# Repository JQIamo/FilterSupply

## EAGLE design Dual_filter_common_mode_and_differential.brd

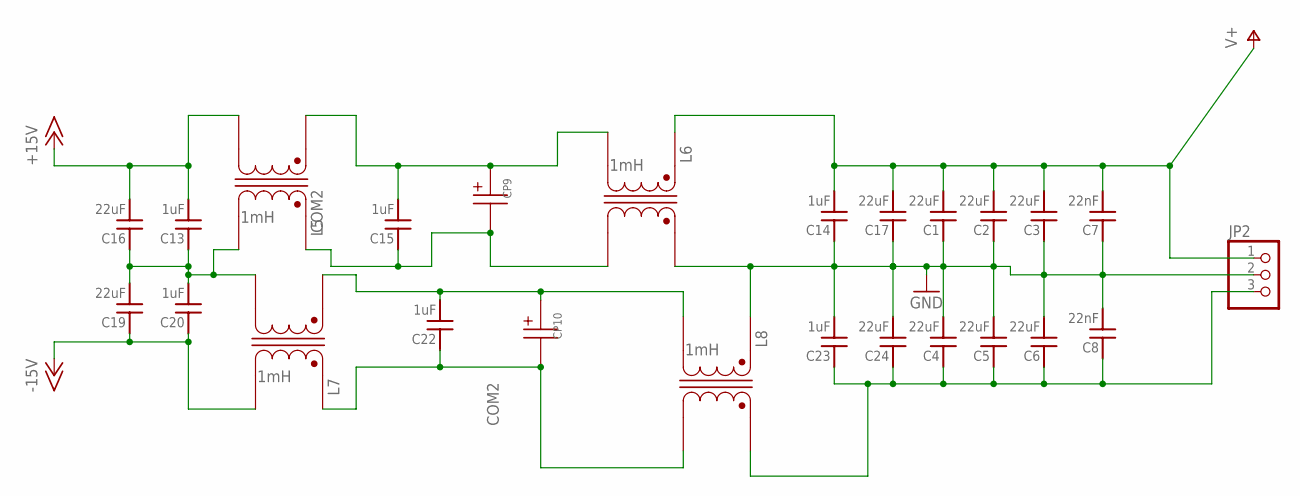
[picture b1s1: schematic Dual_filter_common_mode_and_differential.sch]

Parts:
C1, C2, C3, C4, C5, C6, C16, C17, C19, C24: 22uF; C_MLCC_0805; DIGIKEY 445-9112-1-ND
C7, C8: 22nF; C_MLCC_0306; DIGIKEY 490-4317-1-ND
C13, C14, C15, C20, C22, C23: 1uF; C_MLCC_0805; DIGIKEY 587-5018-1-ND
CP9, CP10: CAP-POLPANASONIC_F; PANASONIC_F
JP2: PINHD-1X3; 1X03; DIGIKEY WM4201-ND
L5, L6, L7, L8: 1mH; COILCRAFT_TRANSFORMER_MSD1260

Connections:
+15V2: C13.P$2 (2), C16.P$2 (2), L5.P$4 (4)
-15V2: C19.P$1 (1), C20.P$1 (1), L7.P$3 (3)
COM2: C13.P$1 (1), C16.P$1 (1), C19.P$2 (2), C20.P$2 (2), L5.P$3 (3), L7.P$4 (4)
GND2: C1.P$1 (1), C2.P$1 (1), C3.P$1 (1), C4.P$2 (2), C5.P$2 (2), C6.P$2 (2), C7.P$1 (1), C8.P$2 (2), C14.P$1 (1), C17.P$1 (1), C23.P$2 (2), C24.P$2 (2), JP2.2, L6.P$2 (2), L8.P$1 (1)
unnamed: C15.P$2 (2), CP9.+, L5.P$2 (2), L6.P$3 (3)
unnamed: C15.P$1 (1), CP9.-, L5.P$1 (1), L6.P$4 (4)
unnamed: C22.P$2 (2), CP10.+, L7.P$2 (2), L8.P$3 (3)
unnamed: C22.P$1 (1), CP10.-, L7.P$1 (1), L8.P$4 (4)
unnamed: C4.P$1 (1), C5.P$1 (1), C6.P$1 (1), C8.P$1 (1), C23.P$1 (1), C24.P$1 (1), JP2.3, L8.P$2 (2)
V+2: C1.P$2 (2), C2.P$2 (2), C3.P$2 (2), C7.P$2 (2), C14.P$2 (2), C17.P$2 (2), JP2.1, L6.P$1 (1)

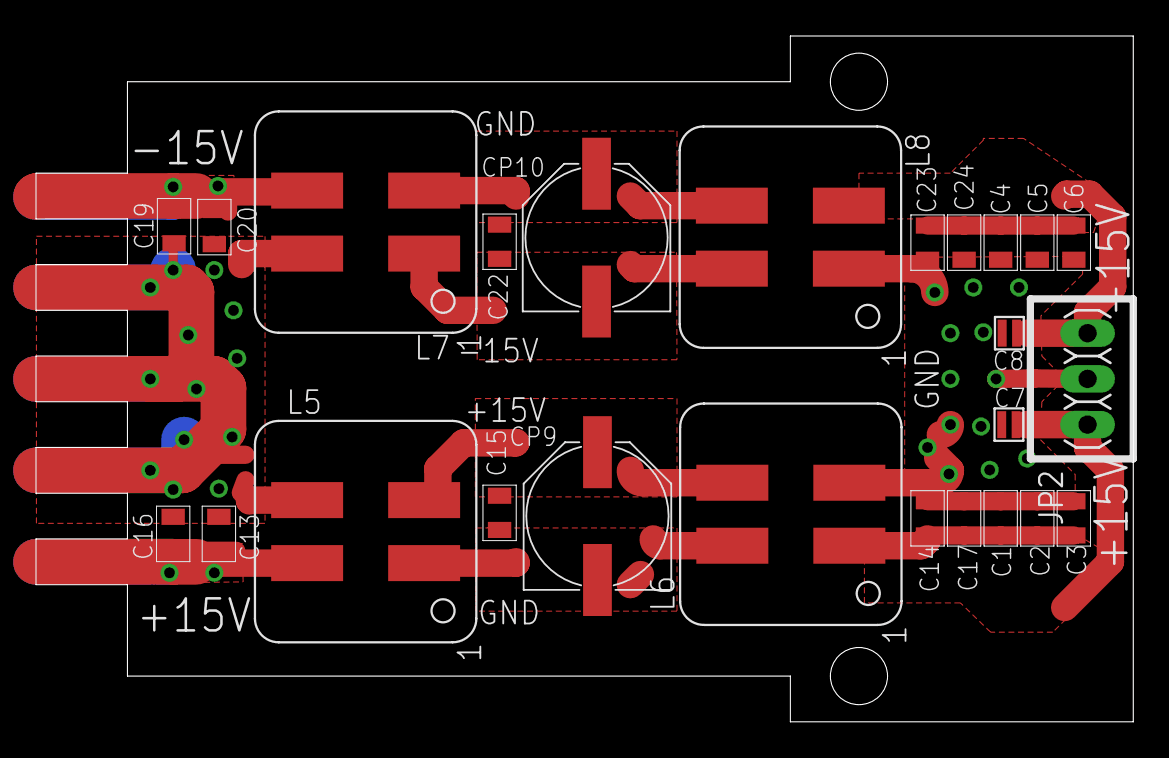
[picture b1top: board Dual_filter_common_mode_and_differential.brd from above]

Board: 2 copper layers, 61.0 x 38.1 mm, 25 parts (0 on the bottom side), 10 nets.

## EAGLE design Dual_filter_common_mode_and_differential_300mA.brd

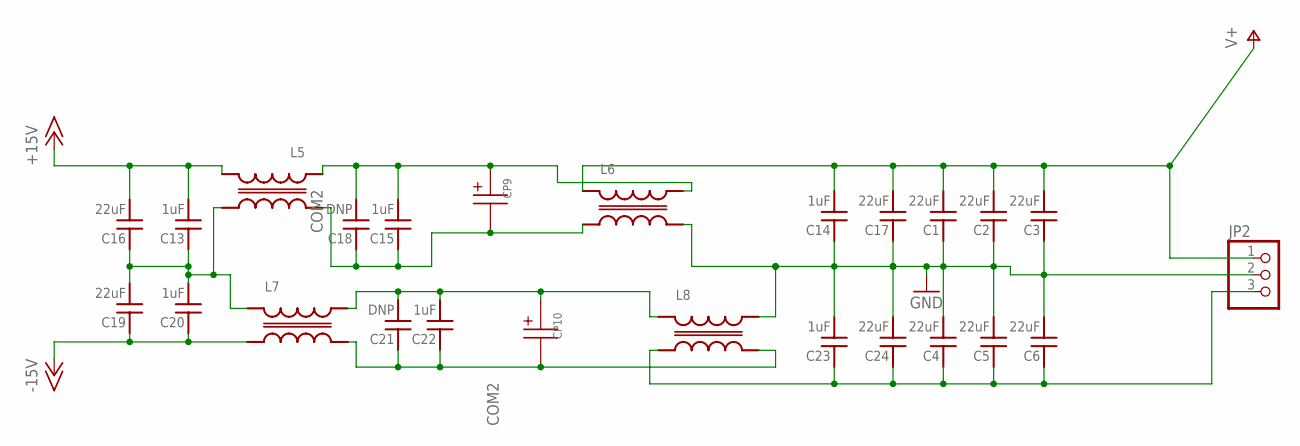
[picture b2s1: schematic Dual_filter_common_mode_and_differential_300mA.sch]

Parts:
C1, C2, C3, C4, C5, C6, C16, C17, C19, C24: 22uF; C_MLCC_0805; DIGIKEY 445-9112-1-ND
C13, C14, C15, C20, C22, C23: 1uF; C_MLCC_0805; DIGIKEY 587-5018-1-ND
C18, C21: DNP; C_MLCC_0805
CP9, CP10: CAP-POLPANASONIC_F; PANASONIC_F
JP2: PINHD-1X3; 1X03; DIGIKEY WM4201-ND
L5, L6, L7, L8: MSD7342

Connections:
+15V2: C13.P$2 (2), C16.P$2 (2), L5.4
-15V2: C19.P$1 (1), C20.P$1 (1), L7.1
COM2: C13.P$1 (1), C16.P$1 (1), C19.P$2 (2), C20.P$2 (2), L5.3, L7.2
GND2: C1.P$1 (1), C2.P$1 (1), C3.P$1 (1), C4.P$2 (2), C5.P$2 (2), C6.P$2 (2), C14.P$1 (1), C17.P$1 (1), C23.P$2 (2), C24.P$2 (2), JP2.2, L6.3, L8.4
unnamed: C15.P$2 (2), C18.P$2 (2), CP9.+, L5.2, L6.4
unnamed: C15.P$1 (1), C18.P$1 (1), CP9.-, L5.1, L6.1
unnamed: C21.P$2 (2), C22.P$2 (2), CP10.+, L7.4, L8.2
unnamed: C21.P$1 (1), C22.P$1 (1), CP10.-, L7.3, L8.3
unnamed: C4.P$1 (1), C5.P$1 (1), C6.P$1 (1), C23.P$1 (1), C24.P$1 (1), JP2.3, L8.1
V+2: C1.P$2 (2), C2.P$2 (2), C3.P$2 (2), C14.P$2 (2), C17.P$2 (2), JP2.1, L6.2

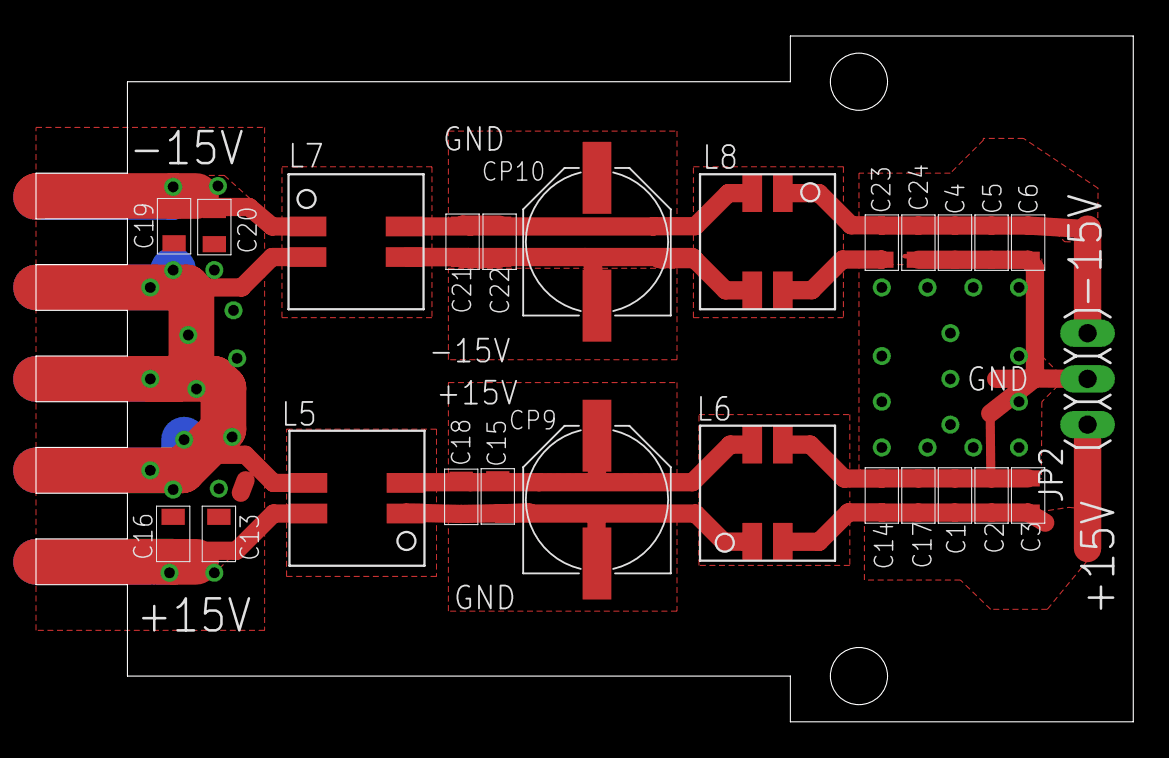
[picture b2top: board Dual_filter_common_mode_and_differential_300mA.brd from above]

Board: 2 copper layers, 61.0 x 38.1 mm, 25 parts (0 on the bottom side), 10 nets.

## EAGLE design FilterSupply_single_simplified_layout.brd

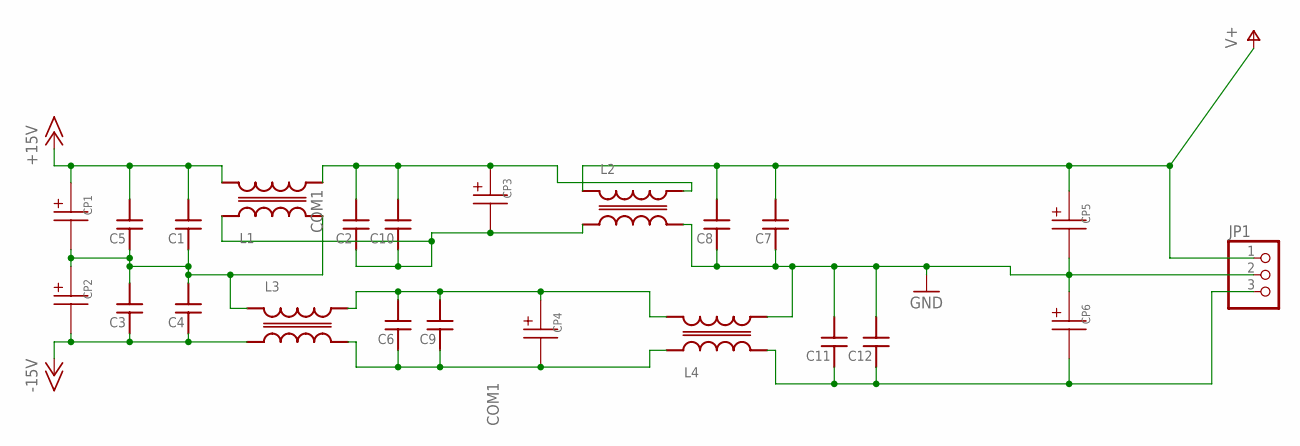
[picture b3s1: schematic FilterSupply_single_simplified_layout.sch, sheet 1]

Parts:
C1, C3, C4, C5: C_MLCC_SMDCMLCC_0805; C_MLCC_0805
C2, C6, C7, C8, C9, C10, C11, C12: C_MLCC_SMDCMLCC_0603; C_MLCC_0603
CP1, CP2, CP3, CP4, CP5, CP6: CAP-POLPANASONIC_F; PANASONIC_F
JP1: PINHD-1X3; 1X03
L1, L2, L3, L4: MSD7342

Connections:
+15V: C1.P$2 (2), C5.P$2 (2), CP1.+, L1.1
-15V: C3.P$1 (1), C4.P$1 (1), CP2.-, L3.1
COM1: C1.P$1 (1), C3.P$2 (2), C4.P$2 (2), C5.P$1 (1), CP1.-, CP2.+, L1.4, L3.2
GND: C7.P$1 (1), C8.P$1 (1), C11.P$2 (2), C12.P$2 (2), CP5.-, CP6.+, JP1.2, L2.3, L4.3
unnamed: C2.P$2 (2), C10.P$2 (2), CP3.+, L1.3, L2.4
unnamed: C2.P$1 (1), C10.P$1 (1), CP3.-, L1.2, L2.1
unnamed: C6.P$2 (2), C9.P$2 (2), CP4.+, L3.4, L4.1
unnamed: C6.P$1 (1), C9.P$1 (1), CP4.-, L3.3, L4.2
unnamed: C11.P$1 (1), C12.P$1 (1), CP6.-, JP1.3, L4.4
V+: C7.P$2 (2), C8.P$2 (2), CP5.+, JP1.1, L2.2

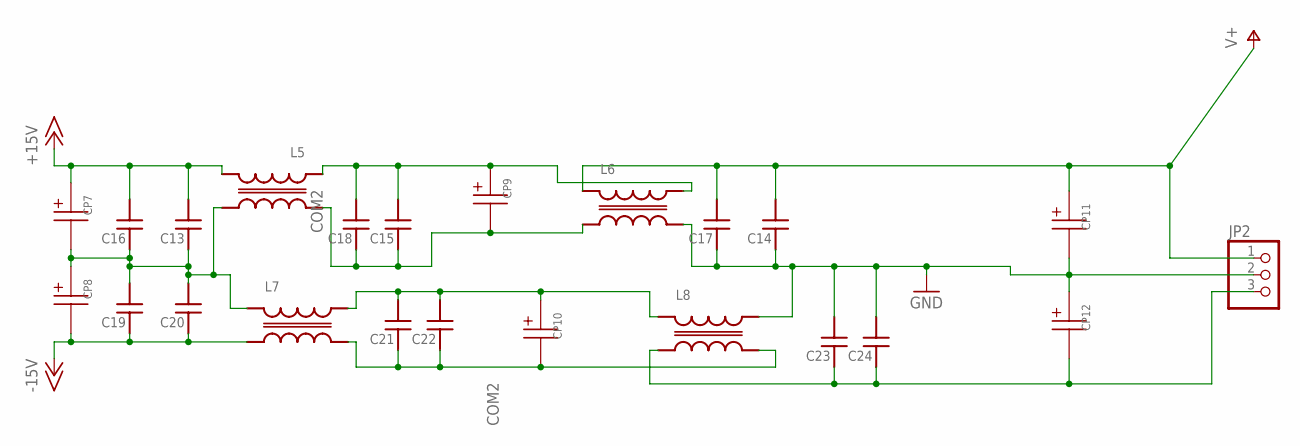
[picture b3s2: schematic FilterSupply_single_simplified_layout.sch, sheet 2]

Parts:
C13, C16, C19, C20: C_MLCC_SMDCMLCC_0805; C_MLCC_0805
C14, C15, C17, C18, C21, C22, C23, C24: C_MLCC_SMDCMLCC_0603; C_MLCC_0603
CP7, CP8, CP9, CP10, CP11, CP12: CAP-POLPANASONIC_F; PANASONIC_F
JP2: PINHD-1X3; 1X03
L5, L6, L7, L8: MSD7342

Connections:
+15V2: C13.P$2 (2), C16.P$2 (2), CP7.+, L5.4
-15V2: C19.P$1 (1), C20.P$1 (1), CP8.-, L7.1
COM2: C13.P$1 (1), C16.P$1 (1), C19.P$2 (2), C20.P$2 (2), CP7.-, CP8.+, L5.3, L7.2
GND2: C14.P$1 (1), C17.P$1 (1), C23.P$2 (2), C24.P$2 (2), CP11.-, CP12.+, JP2.2, L6.3, L8.4
unnamed: C15.P$2 (2), C18.P$2 (2), CP9.+, L5.2, L6.4
unnamed: C15.P$1 (1), C18.P$1 (1), CP9.-, L5.1, L6.1
unnamed: C21.P$2 (2), C22.P$2 (2), CP10.+, L7.4, L8.2
unnamed: C21.P$1 (1), C22.P$1 (1), CP10.-, L7.3, L8.3
unnamed: C23.P$1 (1), C24.P$1 (1), CP12.-, JP2.3, L8.1
V+2: C14.P$2 (2), C17.P$2 (2), CP11.+, JP2.1, L6.2

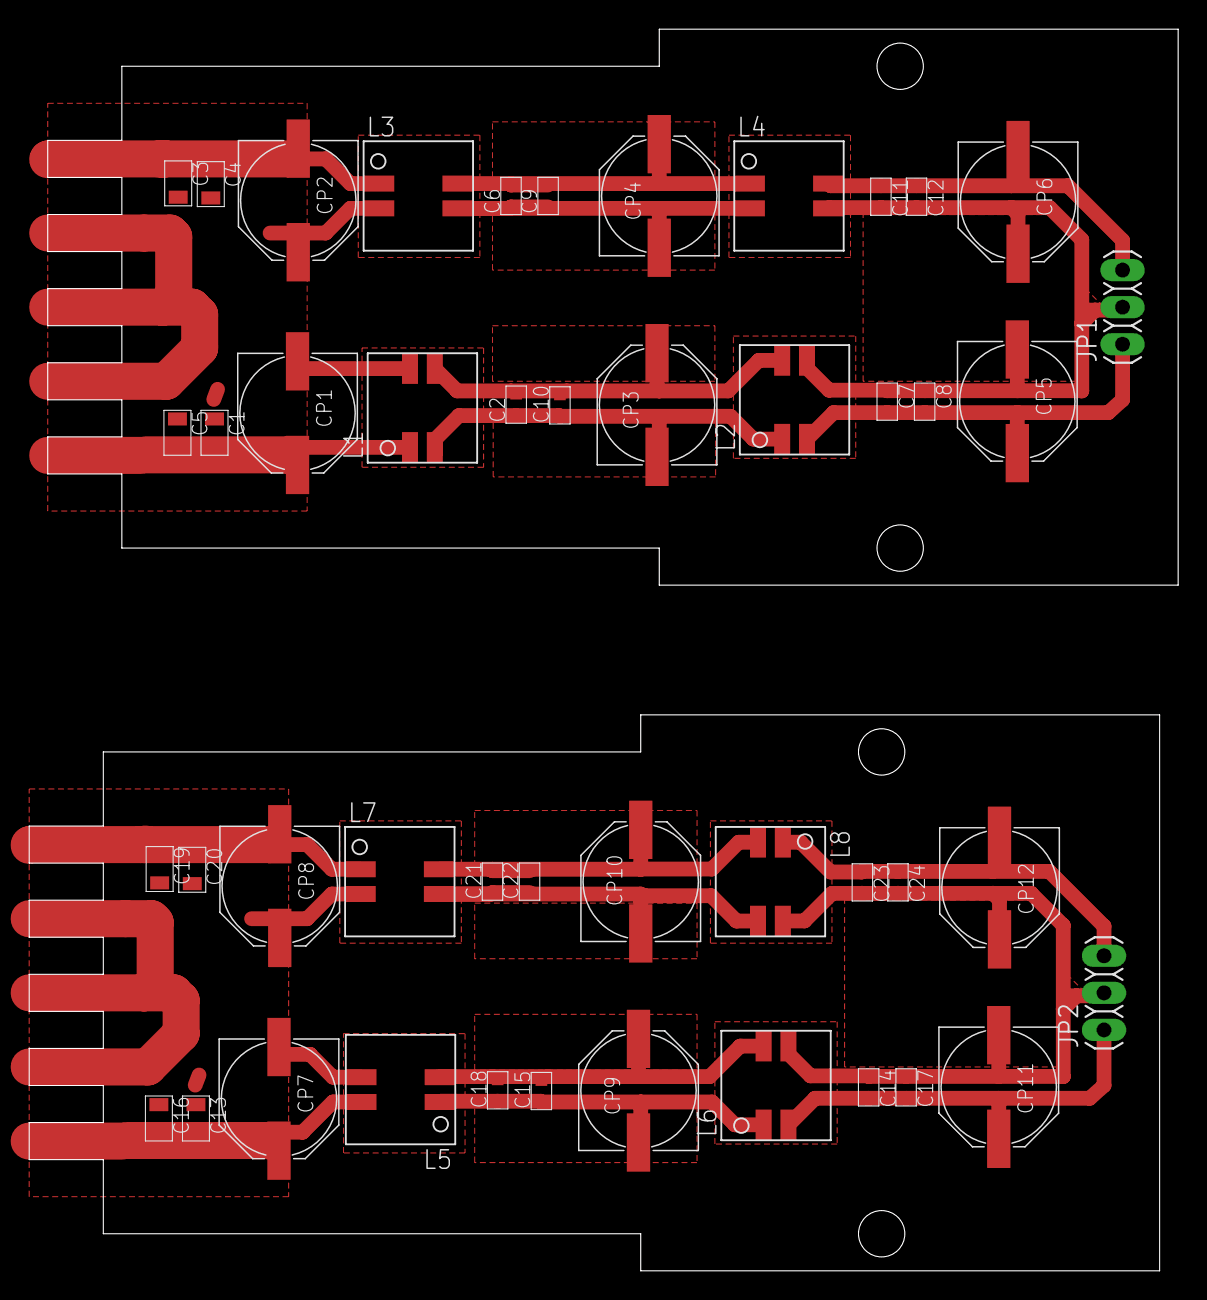
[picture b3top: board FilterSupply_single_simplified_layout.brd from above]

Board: 2 copper layers, 78.7 x 85.1 mm, 46 parts (0 on the bottom side), 20 nets.

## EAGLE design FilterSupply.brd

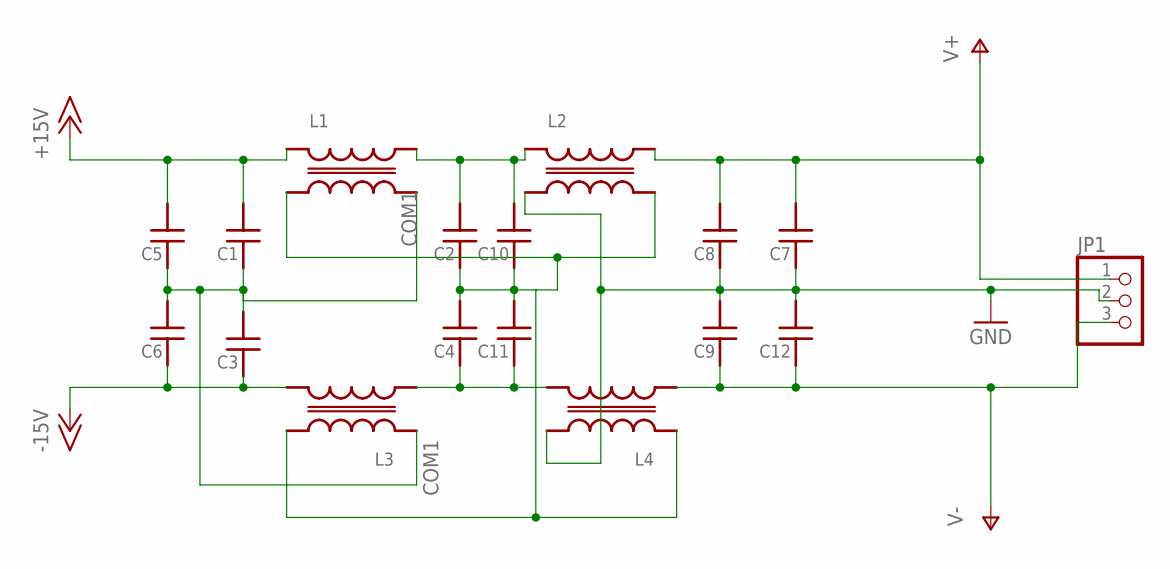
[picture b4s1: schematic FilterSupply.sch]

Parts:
C1, C3, C5, C6: C_MLCC_SMDCMLCC_0805; C_MLCC_0805
C2, C4, C7, C8, C9, C10, C11, C12: C_MLCC_SMDCMLCC_0603; C_MLCC_0603
JP1: PINHD-1X3; 1X03
L1, L2, L3, L4: MSD7342

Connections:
+15V: C1.P$2 (2), C5.P$2 (2), L1.2
-15V: C3.P$1 (1), C6.P$1 (1), L3.3
COM1: C1.P$1 (1), C3.P$2 (2), C5.P$1 (1), C6.P$2 (2), L1.3, L3.2
GND: C7.P$1 (1), C8.P$1 (1), C9.P$2 (2), C12.P$2 (2), JP1.2, L2.1, L4.4
unnamed: C2.P$2 (2), C10.P$2 (2), L1.4, L2.2
unnamed: C2.P$1 (1), C4.P$2 (2), C10.P$1 (1), C11.P$2 (2), L1.1, L2.3, L3.4, L4.2
unnamed: C4.P$1 (1), C11.P$1 (1), L3.1, L4.3
V+: C7.P$2 (2), C8.P$2 (2), JP1.1, L2.4
V-: C9.P$1 (1), C12.P$1 (1), JP1.3, L4.1

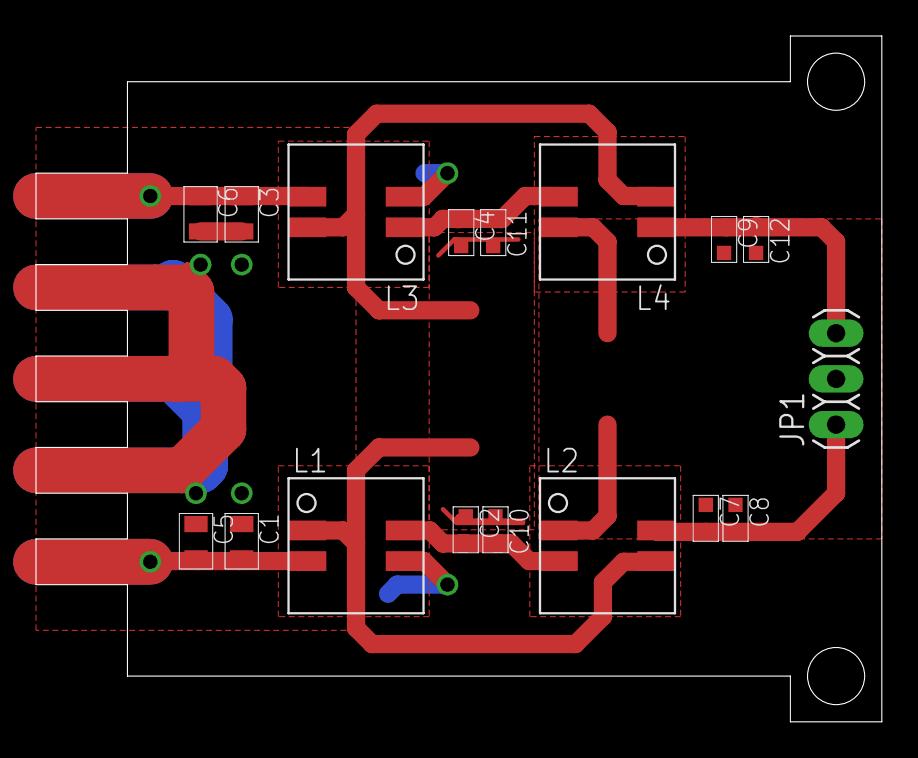
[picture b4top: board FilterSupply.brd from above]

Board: 2 copper layers, 47.0 x 38.1 mm, 17 parts (0 on the bottom side), 9 nets.

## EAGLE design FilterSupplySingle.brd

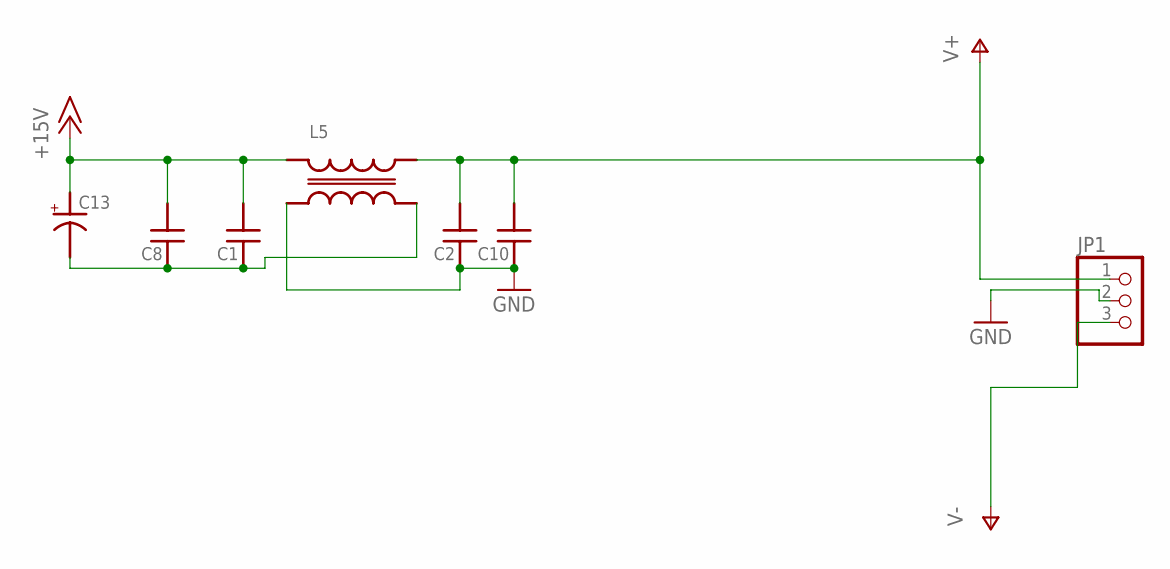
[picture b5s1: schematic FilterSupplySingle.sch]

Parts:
C1, C2: C_MLCC_SMDCMLCC_0805; C_MLCC_0805
C8, C10: C_MLCC_SMDCMLCC_0603; C_MLCC_0603
C13: C_POL_SMDF; PANASONIC_F
JP1: PINHD-1X3; 1X03
L5: MSD7342

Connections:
+15V: C1.P$2 (2), C8.P$2 (2), C13.+, L5.2
GND: C2.P$1 (1), C10.P$1 (1), JP1.2, L5.1
unnamed: C1.P$1 (1), C8.P$1 (1), C13.-, L5.3
V+: C2.P$2 (2), C10.P$2 (2), JP1.1, L5.4
V-: JP1.3

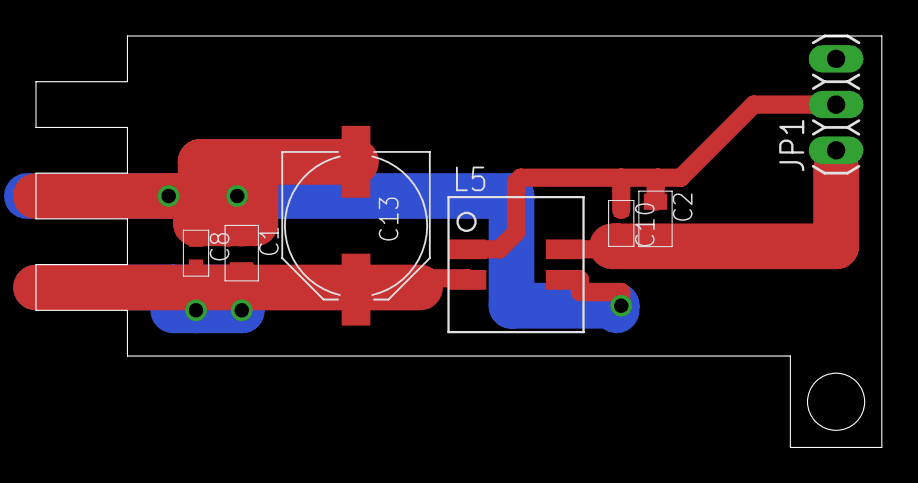
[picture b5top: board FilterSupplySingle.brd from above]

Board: 2 copper layers, 47.0 x 22.9 mm, 7 parts (0 on the bottom side), 4 nets.

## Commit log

2017-05-17 initial commit; modifications coming soon
2017-06-07 three new version of the circuit added
    FilterSupply_single_simplified_layout contains the two test circuits
    used for measurements of the transfer function and residual ripple.
    Dual_filter_common_mode_and_differential_300mA contains a version of the
    circuit using small inductors rated for lower currents
    Dual_filter_common_mode_and_differential is using the larger inductors
    and it is candidate for fabrication. Please check position of mointing
2017-06-09 Switched from CM-DIFF top CM-CM filtering
